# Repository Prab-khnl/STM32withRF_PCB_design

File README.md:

Chip used :- STM32WB55CEU6.

Important Online Note :-
<https://www.st.com/resource/en/application_note/an5165-how-to-develop-rf-hardware-using-stm32wb-microcontrollers-stmicroelectronics.pdf>

![A diagram of a circuit board AI-generated content may be
incorrect.](images/media/image1.png)This is the reference :-

Use STM32CubeIDE to get more information about the Chip :-

![A screenshot of a computer AI-generated content may be
incorrect.](images/media/image2.png)

![A screenshot of a computer AI-generated content may be
incorrect.](images/media/image3.png)Here I have enabled I2C on PB8 and PB9
corresponding to Pin 5 and 6 respectively.

In Kicad, import the board STM32WB55CEUX.

Ground the Pins VSS5MP5, VSSRF and VSS.

![A screen shot of a computer AI-generated content may be
incorrect.](images/media/image4.png)

As illustrated on the reference manual, the Pin VDDUSB, VDDA, VDD, VDD,
VDD and VBAT are connected to 3.3V power supply through bigger capacitor
(4.67uF) and smaller capacitors (100nF : local supply).

![A screen shot of a graph AI-generated content may be
incorrect.](images/media/image5.png)

For VDDRF, connect it to 100nF capacitor along with power supply

![A screenshot of a computer AI-generated content may be
incorrect.](images/media/image6.png)

We need Stepdown converter to step down voltage for lower voltage. For 8
MHz we use 2.2uH inductor and for 4MHz we use 10uF inductor. SMPSLX --
Switch Mode Power Supply

SMPSFB -- Switch Power Supply Feed Back

![A screenshot of a computer AI-generated content may be
incorrect.](images/media/image7.png)

The low frequency oscillator(Crystal) is connected to Pin 2 and 3.

![A screenshot of a computer AI-generated content may be
incorrect.](images/media/image8.png)

![A screenshot of a computer AI-generated content may be
incorrect.](images/media/image9.png)The high frequency
oscillator(Crystal_GND24) are connected to Pin 24 and 25.

We can add resistor in HSC_IN to increase the longevity of oscillator.

![A diagram of a circuit AI-generated content may be
incorrect.](images/media/image10.png)RF Section:-

We need low pass filter for 2.4GHz and 5GHz.

For that we need to create a footprint and symbol of DLF162500LT-5028A1.

![A screenshot of a computer AI-generated content may be
incorrect.](images/media/image11.png)From File, Add library\> DLF162500LT-5028A1

![A screenshot of a computer AI-generated content may be
incorrect.](images/media/image12.png)Go to the Pin table and add pins.

Use the rectangle tool on the right side to draw the rectangle touching
the pins.![A screen shot of a computer AI-generated content may be
incorrect.](images/media/image13.png)

Use the Text "T" tool to add the text label "2.4GHz- 2.5GHz".

Save the symbol. Now it's time to create the physical footprint of the
symbol.

Use this footprint editor to create the new footprint.![A screenshot of
a computer AI-generated content may be
incorrect.](images/media/image14.png)

Go to file \> Add library and name your library.

Here the newly added library is STM32_RF_LowPassFilterFootPrint

![A screenshot of a computer AI-generated content may be
incorrect.](images/media/image15.png)

In the new library, add new Footprint and name it as Component name eg.
"DLF162500LT-5028A1"

This is the dimension of
[footprint](https://product.tdk.com/system/files/dam/doc/product/rf/rf/filter/catalog/rf_lpf_dlf162500lt-5028a1_en.pdf).

![A blueprint of a diagram AI-generated content may be
incorrect.](images/media/image16.png)

![A screenshot of a phone AI-generated content may be
incorrect.](images/media/image17.png)Add pad from here.

According to the dimension, the centre of origin:-

X : ½ ( 0.275 + 0.45) + 0.25 = 0.6125.

Y : ½ (0.245 +0.21) = 0.2275

This is the position and dimensions of pad1 :-

![A screenshot of a computer AI-generated content may be
incorrect.](images/media/image18.png)

This is the position and dimensions of pad 3:-

![A screenshot of a computer AI-generated content may be
incorrect.](images/media/image19.png)

This is the position and dimensions of pad 2:-

![A screenshot of a computer AI-generated content may be
incorrect.](images/media/image20.png)

This is the position and dimensions of pad 4:-

![A screenshot of a computer AI-generated content may be
incorrect.](images/media/image21.png)

Download 3D Model of symbol from ![A screenshot of a computer
AI-generated content may be
incorrect.](images/media/image22.png)ultralibrarian in .step format.

![A screenshot of a computer AI-generated content may be
incorrect.](images/media/image23.png)In Kicad go to footprint properties and
add the 3d model. Our pad aligns with physical pins.

![A screen shot of a computer AI-generated content may be
incorrect.](images/media/image24.png)With silkscreen layer selected, click
circle tool to add indicator for pin 1.

Using the symbol editor, assign newly created footprint to the symbol we
just created.

![A screenshot of a computer AI-generated content may be
incorrect.](images/media/image25.png)

Place newly created symbol to the schematic and connect to pin 1.![A
diagram of a circuit AI-generated content may be
incorrect.](images/media/image26.png)

Add a Co-Axial connector.

![A screenshot of a computer AI-generated content may be
incorrect.](images/media/image27.png)

![A computer diagram of a circuit board AI-generated content may be
incorrect.](images/media/image28.png)This is our current progress.

Now, we need to add the programming interface.

The PA 13, PA 14 and PA3 can be used to program and debug the board.
Along with those pins NRST has to be low (0) for programming mode and
high (1) on normal mode.

![A screenshot of a computer AI-generated content may be
incorrect.](images/media/image29.png)

Connect the tag connector "Conn_ARM_SWD_TagConnect_TC2030". Connect the
tag connector to respective pin as shown. For NRST( Reset) pin connect
it through 100nF capacitor at Pin 7.

![A diagram of a circuit board AI-generated content may be
incorrect.](images/media/image30.png)

PH3 is bootload pin and should 0 be on bootload. When the pin Switch is
not pressed, the PH3 is grounded but on pressed, the connection acts as
lowpass RC filter.

![A diagram of a circuit AI-generated content may be
incorrect.](images/media/image31.png)

Add USB "USB_C_Receptacle_USB2.0_16P" and we are going to use pin 37 and
38.

![A computer screen shot of a circuit board AI-generated content may be
incorrect.](images/media/image32.png)

Add a USB protector between the USB Connector and Pins.

![A diagram of a circuit board AI-generated content may be
incorrect.](images/media/image33.png)

The D- pins and D+ pins are connected each other and then to Pins 1 and
3 respectively on the USB protector. The VBUS is connected to Pin 5. Pin
6 and 4 are connected to Pin 37 and 37 respectively on the STM32
Microcontroller.

The pull down resistors are tied on the Pin A5 and B5.

Convert 5V of VBUS to 3.3V using LDO voltage regulator.

Search LDO voltage regulator by putting requirement on mouser. Add a
voltage regulator "MIC5365-3.3YD5" to get 3.3V output.

![A computer circuit board with many wires AI-generated content may be
incorrect.](images/media/image34.png)

![A diagram of a circuit AI-generated content may be
incorrect.](images/media/image35.png)Add a Peripheral connection on PA2 and PA2
using Generic 01\*04 Connector.

![A screenshot of a computer AI-generated content may be
incorrect.](images/media/image36.png)Use PA7 for PWM Output signal generation.

Add LED to Pin 16 (PA7) and add current limiting 220 Ohm resistor.

![A screenshot of a computer AI-generated content may be
incorrect.](images/media/image37.png)

![A computer diagram of a circuit board AI-generated content may be
incorrect.](images/media/image38.png)Overall schematic :-

![A computer screen shot of a computer program AI-generated content may
be incorrect.](images/media/image39.png)Run electric rule checker and make sure all
wirings are correct.

Add footprint to the capacitor.

Add footprint to all the components.

![A screenshot of a computer AI-generated content may be
incorrect.](images/media/image41.png)

Create Bill of Materials for all the components.

![A screenshot of a computer AI-generated content may be
incorrect.](images/media/image42.png)

![A screenshot of a computer AI-generated content may be
incorrect.](images/media/image43.png)Add netclass to group the components.

Setup layers

![A screenshot of a computer AI-generated content may be
incorrect.](images/media/image44.png)

Select 4 layers and impedance controlled

![A screenshot of a computer AI-generated content may be
incorrect.](images/media/image45.png)

![A screenshot of a computer AI-generated content may be
incorrect.](images/media/image46.png)Select these layer width

Lead free copper

![A screenshot of a computer AI-generated content may be
incorrect.](images/media/image47.png)

Solder Mask

![A screenshot of a computer AI-generated content may be
incorrect.](images/media/image48.png)

![A screenshot of a computer AI-generated content may be
incorrect.](images/media/image49.png)Fill in these board capabilities and
requirements

![A screenshot of a computer AI-generated content may be
incorrect.](images/media/image50.png)Board rule

![A screenshot of a computer AI-generated content may be
incorrect.](images/media/image51.png)These tracks are calculated on 50 ohm
impedance.

Press Ok

Multi layer PCB![A diagram of a layer of copper layer AI-generated
content may be
incorrect.](images/media/image52.png)

Press F8 to apply the footprints

![A computer screen shot of a computer AI-generated content may be
incorrect.](images/media/image53.png)This is the current 3D view:-

Update the 3D Model STEP file for J2 connector downloaded from
[MOLEX](https://www.molex.com/en-us/products/part-detail/530480410).

![A computer screen shot of a computer AI-generated content may be
incorrect.](images/media/image54.png)

Add 3D model for STM32 from
[here](https://gitlab.com/kicad/libraries/kicad-packages3D/-/blob/5.1.10/Package_DFN_QFN.3dshapes/QFN-48-1EP_7x7mm_P0.5mm_EP5.6x5.6mm.step)

![A screenshot of a computer AI-generated content may be
incorrect.](images/media/image55.png)

3d model can be downloaded from here:-

> 3D content central
>
> Grabcad

![A screenshot of a computer AI-generated content may be
incorrect.](images/media/image56.png)Select blue color for SWD routing

Select net colors to blue for all

![A screenshot of a computer AI-generated content may be
incorrect.](images/media/image57.png)Do the same all others

Create a layout

Select 1 mmm grid

![A machine with colorful lights AI-generated content may be
incorrect.](images/media/image58.png)Move the chip by moving around with M.

Move critical section first like RF, USB connector close to
microcontroller. Also keep crystal and power close to microcontroller.

Debug,BOOT0 , Reset, TX and RX are less critical. BI coupling capacitor
needs to be close .

![A computer screen shot of a computer chip AI-generated content may be
incorrect.](images/media/image59.png)Keep Connector to left of IC.

Place USB connector to left of tag connector and rotate as indicated.

![A computer screen shot of a computer chip AI-generated content may be
incorrect.](images/media/image60.png)

![A computer screen shot of a computer AI-generated content may be
incorrect.](images/media/image61.png)Place RF connector to right of IC and place
filter in between the IC and connector.

Place the crystal as indicated.

![A computer chip with many colors AI-generated content may be
incorrect.](images/media/image62.png)

![A computer screen shot of a computer chip AI-generated content may be
incorrect.](images/media/image63.png)Place the L1, L2 and C14 to top of IC for
now

Place UART connector and resistor to bottom of IC.

![A computer chip with many different colors AI-generated content may be
incorrect.](images/media/image64.png)

![A computer screen shot of a computer AI-generated content may be
incorrect.](images/media/image65.png)Place USB protector as shown

Place the RF components as shown

![A screenshot of a video game AI-generated content may be
incorrect.](images/media/image66.png)

![A computer chip with many different components AI-generated content
may be incorrect.](images/media/image67.png)This is the current 3D view

Place capacitor to crystal oscillator

![A computer screen shot of a computer AI-generated content may be
incorrect.](images/media/image68.png)

![A computer screen shot of a computer AI-generated content may be
incorrect.](images/media/image69.png)Finetune this SMP power supply layout.

Place RF decoupling capacitor close to Pad 23

![A screenshot of a computer AI-generated content may be
incorrect.](images/media/image70.png)

Place another capacitor for pin 20

![A screenshot of a computer AI-generated content may be
incorrect.](images/media/image71.png)

Place capacitor like this near pin 40 to make room to route trace for
Serial DIO

![A computer chip with numbers and symbols AI-generated content may be
incorrect.](images/media/image72.png)

Place decoupling capacitor for pin 34 and 35

![A screenshot of a computer AI-generated content may be
incorrect.](images/media/image73.png)

![A computer chip with many different colored lights AI-generated
content may be
incorrect.](images/media/image74.png)Re arrange this section

Make a room for reset pin

![A computer chip with many different colored lights AI-generated
content may be
incorrect.](images/media/image75.png)

![A computer screen shot of a computer chip AI-generated content may be
incorrect.](images/media/image76.png)Move SMP close to microcontroller but put crystal
away

![A screenshot of a video game AI-generated content may be
incorrect.](images/media/image77.png)Place LDO 3.3V regulator as shown

Place resistors around USB C connector

![A computer screen shot of a computer AI-generated content may be
incorrect.](images/media/image78.png)

Place reset capacitor C13

![A computer chip with many different colors AI-generated content may be
incorrect.](images/media/image79.png)

Place the switch and resistors around the switch

![A computer screen shot of a computer AI-generated content may be
incorrect.](images/media/image80.png)

![A computer chip with many different components AI-generated content
may be incorrect.](images/media/image81.png)This is the current 3D layout of the board

![A computer screen shot of a computer program AI-generated content may
be incorrect.](images/media/image82.png)Define board out line. Select Edge.cuts
layer. Select line tool and draw the line.

You can also use the arc tool to draw the arc around the edge of the
board

![A screen shot of a computer AI-generated content may be
incorrect.](images/media/image83.png)

Start routing with most critical component. We can use top layer for
power and bottom layer for ground.

Signal -- GND -GND -Signal ( 4 layers) GNB Layer in Inner 1 and Inner 2

![A screenshot of a computer AI-generated content may be
incorrect.](images/media/image84.png)Select In1.Cu. Add a GND Layer and adjust
the electrical properties.

Draw outline of the board. Select B to fill the board.

![A computer screen shot of a circuit board AI-generated content may be
incorrect.](images/media/image85.png)

Add a mounting hole with this footprint.\
![A screenshot of a computer AI-generated content may be
incorrect.](images/media/image86.png)

Add fiducial marker to automate assembly.

![A screenshot of a computer AI-generated content may be
incorrect.](images/media/image87.png)

![A computer screen shot of a computer AI-generated content may be
incorrect.](images/media/image88.png)Place the mounting hole and marker as
shown.

Use Via to jump between layer 0.7mm/0.33mm via

![A screenshot of a computer AI-generated content may be
incorrect.](images/media/image89.png)

![A screenshot of a computer AI-generated content may be
incorrect.](images/media/image90.png)Connect the via and track with GND Pad

Copy and paste these tracks and via on 0402 components.

![A computer screen shot of a computer chip AI-generated content may be
incorrect.](images/media/image91.png)

Place the via on the chips for heat sinking purpose.

![A green screen with white text AI-generated content may be
incorrect.](images/media/image92.png)

![A computer screen shot of a computer chip AI-generated content may be
incorrect.](images/media/image93.png)Add 3.3V via

For RF trace we would use 0.190mm trace for control impedance of 50 Ohm

![A screenshot of a computer AI-generated content may be
incorrect.](images/media/image94.png)Set the width of RF in NetClass properties.

![A computer screen shot of a computer AI-generated content may be
incorrect.](images/media/image95.png)Route the RF section

Route the high frequency HSC clock.

![A computer screen shot of a circuit board AI-generated content may be
incorrect.](images/media/image96.png)

![A computer screen shot of a circuit board AI-generated content may be
incorrect.](images/media/image97.png)Trace Low frequency clocks

Add 0.250 mm track width for Switch Model. Press W to increase the mad
width.

![A screenshot of a computer AI-generated content may be
incorrect.](images/media/image98.png) We can also use this for the feedback

Ground the Pin

![A screen shot of a computer AI-generated content may be
incorrect.](images/media/image99.png)

Use differential pair by pressing 6 and selecting the netclass "USB" to
route the two usb wires together

![A screenshot of a computer AI-generated content may be
incorrect.](images/media/image100.png)Route the rest

![A computer screen shot of a circuit board AI-generated content may be
incorrect.](images/media/image101.png)

![A screenshot of a computer AI-generated content may be
incorrect.](images/media/image102.png)Route the UART Section

![A computer screen shot of a circuit board AI-generated content may be
incorrect.](images/media/image103.png)Use Via to jump between top and bottom
layer to route the Boot0

![A computer screen shot of a computer AI-generated content may be
incorrect.](images/media/image104.png)We can place the GND via near transitional jump for
higher bandwidth circuit

![A computer screen shot of a circuit board AI-generated content may be
incorrect.](images/media/image105.png)Complete the rest of the USB connector section.

Complete the led section

![A screenshot of a video game AI-generated content may be
incorrect.](images/media/image106.png)

Select Mounting hole. Select 2 and Press E to change the copper zones to
Solid

![A screenshot of a computer AI-generated content may be
incorrect.](images/media/image107.png)

![A computer screen shot of a circuit board AI-generated content may be
incorrect.](images/media/image108.png)Connect the 5Vs power supply traces and
draw polygon layer for 3V power supply.

![A computer screen shot of a star AI-generated content may be
incorrect.](images/media/image109.png)Select only the bottom select by selecting
"Hide all planes but active" and draw traces connecting 3.3V Vias

The other way to do is to convert the bottom layer polygon to 3.3V
layer. For that select the GNB polygon, Crl +C and paste it. Press E to
select the new layer and select 3.3V for bottom layer

![A screenshot of a computer AI-generated content may be
incorrect.](images/media/image110.png)

![A screenshot of a video game AI-generated content may be
incorrect.](images/media/image111.png)Now, 3.3V is the bottom layer.

![A computer screen shot of a computer chip AI-generated content may be
incorrect.](images/media/image112.png)Connect rest of the 3.3V and GNB
connections

For copper balancing, change the top copper layer to GND. To do this
Select In1.cu and double click on GND layer. Choose F.CU to GND Layer.

![A screenshot of a computer AI-generated content may be
incorrect.](images/media/image113.png)

Press B to repull and now we have GND layer on top layer.

![A computer screen shot of a circuit board AI-generated content may be
incorrect.](images/media/image114.png)

These coppers which are really close could affect the impedance for the
RF section. The traces should be at least 3 times the dielectric width
away.

![A video game screen with a green background AI-generated content may
be incorrect.](images/media/image115.png)

Currently the dielectric is 0.1mm. We want the separation to be at least
0.3mm.

![A screenshot of a computer AI-generated content may be
incorrect.](images/media/image116.png)

Draw keypad area to keep out the copper fills.

![A screenshot of a computer AI-generated content may be
incorrect.](images/media/image117.png)

Press B to keep out the copper fills.

![A screenshot of a video game AI-generated content may be
incorrect.](images/media/image118.png)

![A screenshot of a computer AI-generated content may be
incorrect.](images/media/image119.png)Instead, we can also change the clearance
to 0.35mm.

![A screenshot of a computer AI-generated content may be
incorrect.](images/media/image120.png)We can also try thermal relief to have
smaller gap and larger spoke width.

We need to Stitching via to reduce impedance between ground plane and
vias. Place it around the board. The spacing can be calculated as

(3 \* 10\^8)/ (20\* sqrt(4.29) \*2.4\*10\^9) \*10\^3

Speed of light / 20 \* Sqrt of dielectric constant \* Frequency

=3mm

![A computer screen shot of a circuit board AI-generated content may be
incorrect.](images/media/image121.png)

![A green circuit board with many small chips AI-generated content may
be incorrect.](images/media/image122.png)This is what the board looks like

Move the marking on the silkscreen so that the markings do not overlap.

![A computer screen shot of a computer chip AI-generated content may be
incorrect.](images/media/image123.png)

We can add teardrops for smooth transition between wide and narrow
traces. Else, go to tools\> Remove unused pads

![A screenshot of a computer AI-generated content may be
incorrect.](images/media/image124.png)

Run DRC Checker.

Fix clearance violation by decreasing the pad size.

![A screen shot of a computer AI-generated content may be
incorrect.](images/media/image125.png)

Reduce the pad size in X axis.

![A screenshot of a computer AI-generated content may be
incorrect.](images/media/image126.png)

To solve this error, uncheck the fiducial marker pad from F.Cu.

![A screenshot of a computer AI-generated content may be
incorrect.](images/media/image127.png)

To fix it, connect the pad to GND via.

Clearance violation

![A screenshot of a computer AI-generated content may be
incorrect.](images/media/image129.png)

Move the GND via.

![A computer screen shot of a green and red line AI-generated content
may be
incorrect.](images/media/image130.png)

Now, we have 0 DRC violation

![A computer screen shot of a computer AI-generated content may be
incorrect.](images/media/image131.png)

Final Board:-

![A computer screen shot of a green circuit board AI-generated content
may be
incorrect.](images/media/image132.png)

Go to Tools \> Generate Bill of Materials to generate the components
needed and their designator values on the PCB.

![A screenshot of a computer AI-generated content may be
incorrect.](images/media/image133.png)

We need to know the coordinate of the components to know where the
components are on the PCB.

At the Place \> Grid Place Origin and Drill Place Origin, put the origin
to bottom left.

![A green screen with black dots and white text AI-generated content may
be incorrect.](images/media/image134.png)

Go to files \> Fabrication Output \> Generate Placement files

![A screenshot of a computer AI-generated content may be
incorrect.](images/media/image135.png)

.pos file will appear on the project directory.

We now need the Gerber files. Go to files \> Fabrication Output \>
Generate Gerber files. Include the following layers and options.

![A screenshot of a computer AI-generated content may be
incorrect.](images/media/image136.png)

Go to generate layers and generate drill files.

You can check the gerber files using Kicad Gerber viewer. These are the
files we need to upload to manufacturer ( Gerber, Position files and
Bill of Materials). We can also send additional notes such as Control
Impedance, clearance and so on.

![A computer screen shot of a computer AI-generated content may be
incorrect.](images/media/image137.png)

To order the PCB, create and upload zip files of Gerber.

![A screenshot of a computer AI-generated content may be
incorrect.](images/media/image138.png)

It automatically identified the board requirements

![A screenshot of a computer AI-generated content may be
incorrect.](images/media/image139.png)

![A screenshot of a computer AI-generated content may be
incorrect.](images/media/image140.png)Select these options

We can have PCBway assemble the whole PCB

![A screenshot of a computer AI-generated content may be
incorrect.](images/media/image141.png)

Then you will have to upload Bill of Material files, Centroid files
(CPL.txt) and assembly drawing optional).

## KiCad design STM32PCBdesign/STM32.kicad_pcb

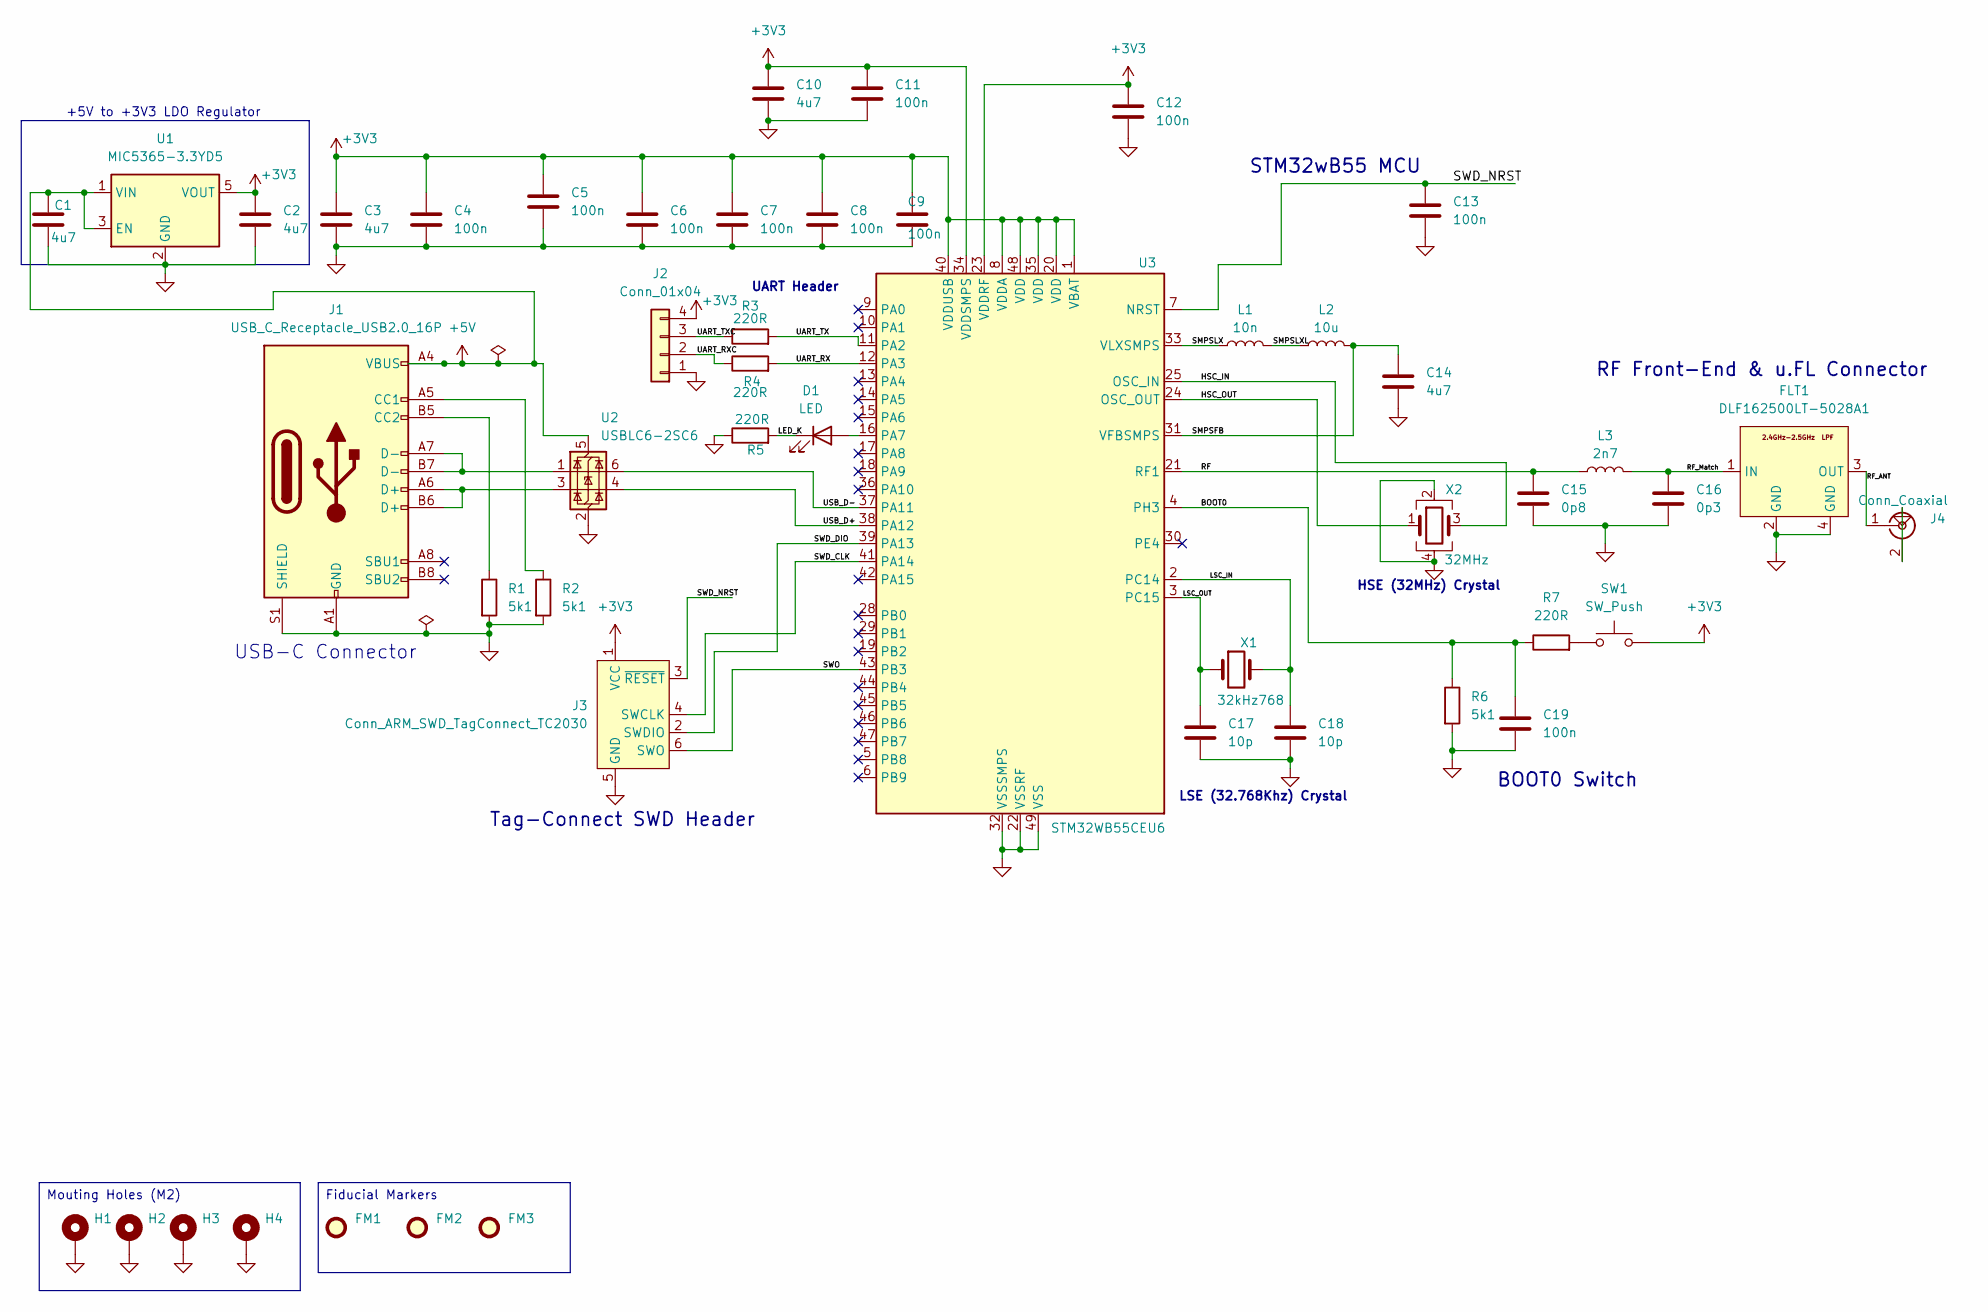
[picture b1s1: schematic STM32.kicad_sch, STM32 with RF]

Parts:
C1, C2, C3, C10, C14: 4u7; C_0603_1608Metric; Manufacturer Part Number 0603YD475MAT2A
C4, C5, C6, C7, C8, C9, C11, C12, C13, C19: 100n; C_0402_1005Metric; Manufacturer Part Number 04023C104KAT2A
C15: 0p8; C_0402_1005Metric; Manufacturer Part Number GRM1555C1HR80BA01D
C16: 0p3; C_0402_1005Metric; Manufacturer Part Number GRM1555C1HR30WA01D
C17, C18: 10p; C_0402_1005Metric; Manufacturer Part Number 04025A100JAT4A
D1: LED; LED_0402_1005Metric; Manufacturer Part Number 150040RS73240
FLT1: DLF162500LT-5028A1; Manufacturer Part Number DLF162500LT-5028A1
FM1, FM2, FM3: Fiducial; Fiducial_1mm_Mask2mm
H1, H2, H3, H4: MountingHole_Pad; MountingHole_2.2mm_M2_Pad_Via
J1: USB_C_Receptacle_USB2.0_16P; USB_C_Receptacle_GCT_USB4105-xx-A_16P_TopMnt_Horizontal; Manufacturer Part Number USB4105-GF-A
J2: Conn_01x04; Molex_CLIK-Mate_502386-0470_1x04-1MP_P1.25mm_Horizontal; Manufacturer Part Number 53048-0410
J3: Conn_ARM_SWD_TagConnect_TC2030; Tag-Connect_TC2030-IDC-FP_2x03_P1.27mm_Vertical
J4: Conn_Coaxial; U.FL_Hirose_U.FL-R-SMT-1_Vertical; Manufacturer Part Number U.FL-R-SMT(01)
L1: 10n; L_0402_1005Metric; Manufacturer Part Number LQG15HS18NJ02D
L2: 10u; L_0805_2012Metric; Manufacturer Part Number LQM21FN100M70L
L3: 2n7; L_0402_1005Metric; Manufacturer Part Number LQG15HS2N7S02D
R1, R2, R6: 5k1; R_0402_1005Metric; Manufacturer Part Number RC0603FR-075K1L
R3, R4, R5, R7: 220R; R_0402_1005Metric; Manufacturer Part Number RC0402FR-07221RL
SW1: SW_Push; SW_SPST_CK_RS282G05A3; Manufacturer Part Number RS282G05A3SMRT
U1: MIC5365-3.3YD5; TSOT-23-5; Manufacturer Part Number MIC5365-3.3YC5-TR
U2: USBLC6-2SC6; SOT-23-6; Manufacturer Part Number USBLC6-2SC6
U3: STM32WB55CEU6; QFN-48-1EP_7x7mm_P0.5mm_EP5.6x5.6mm; Manufacturer Part Number STM32WB55CEU6
X1: 32kHz768; Crystal_SMD_2012-2Pin_2.0x1.2mm; Manufacturer Part Number NX2012SA-32.768K-STD-MUB-1
X2: 32MHz; Crystal_SMD_2016-4Pin_2.0x1.6mm; Manufacturer Part Number NX2016SA-32M-EXS00A-CS06465

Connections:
+3V3: C2.1, C3.1, C4.1, C5.1, C6.1, C7.1, C8.1, C9.1, C10.1, C11.1, C12.1, J2.4, J3.1 (VCC), SW1.2, U1.5 (VOUT), U3.1 (VBAT), U3.8 (VDDA), U3.20 (VDD), U3.23 (VDDRF), U3.34 (VDDSMPS), U3.35 (VDD), U3.40 (VDDUSB), U3.48 (VDD)
+5V: C1.1, J1.A4 (VBUS), J1.A9 (VBUS), J1.B4 (VBUS), J1.B9 (VBUS), U1.1 (VIN), U1.3 (EN), U2.5 (VBUS)
/BOOT0: C19.1, R6.1, R7.1, U3.4 (PH3)
/HSC_IN: U3.25 (OSC_IN), X2.3
/HSC_OUT: U3.24 (OSC_OUT), X2.1
/LED_K: D1.1 (K), R5.2
/LSC_IN: C18.1, U3.2 (PC14), X1.2
/LSC_OUT: C17.1, U3.3 (PC15), X1.1
/RF: C15.1, L3.1, U3.21 (RF1)
/RF_ANT: FLT1.3 (OUT), J4.1 (In)
/RF_Match: C16.1, FLT1.1 (IN), L3.2
/SMPSFB: C14.1, L2.2, U3.31 (VFBSMPS)
/SMPSLX: L1.1, U3.33 (VLXSMPS)
/SMPSLXL: L1.2, L2.1
/SWD_CLK: J3.4 (SWCLK), U3.41 (PA14)
/SWD_DIO: J3.2 (SWDIO), U3.39 (PA13)
/SWD_NRST: C13.1, J3.3 (~RESET), U3.7 (NRST)
/SWO: J3.6 (SWO), U3.43 (PB3)
/UART_RX: R4.2, U3.12 (PA3)
/UART_RXC: J2.2, R4.1
/UART_TX: R3.2, U3.11 (PA2)
/UART_TXC: J2.3, R3.1
/USB_D+: U2.4 (I/O2), U3.38 (PA12)
/USB_D-: U2.6 (I/O1), U3.37 (PA11)
GND: C1.2, C2.2, C3.2, C4.2, C5.2, C6.2, C7.2, C8.2, C9.2, C10.2, C11.2, C12.2, C13.2, C14.2, C15.2, C16.2, C17.2, C18.2, C19.2, FLT1.2 (GND), FLT1.4 (GND), H1.1, H2.1, H3.1, H4.1, J1.A1 (GND), J1.A12 (GND), J1.B1 (GND), J1.B12 (GND), J1.S1 (SHIELD), J2.1, J3.5 (GND), J4.2 (Ext), R1.2, R2.2, R5.1, R6.2, U1.2 (GND), U2.2 (GND), U3.22 (VSSRF), U3.32 (VSSSMPS), U3.49 (VSS), X2.2, X2.4
unnamed: D1.2 (A), U3.16 (PA7)
unnamed: J1.A5 (CC1), R2.1
unnamed: J1.B5 (CC2), R1.1
unnamed: J1.A6 (D+), J1.B6 (D+), U2.3 (I/O2)
unnamed: J1.A7 (D-), J1.B7 (D-), U2.1 (I/O1)
unnamed: R7.2, SW1.1

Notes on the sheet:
BOOT0 Switch
RF Front-End & u.FL Connector
UART Header
+5V to +3V3 LDO Regulator
STM32wB55 MCU
Tag-Connect SWD Header
HSE (32MHz) Crystal
USB-C Connector
LSE (32.768Khz) Crystal
Fiducial Markers
Mouting Holes (M2)

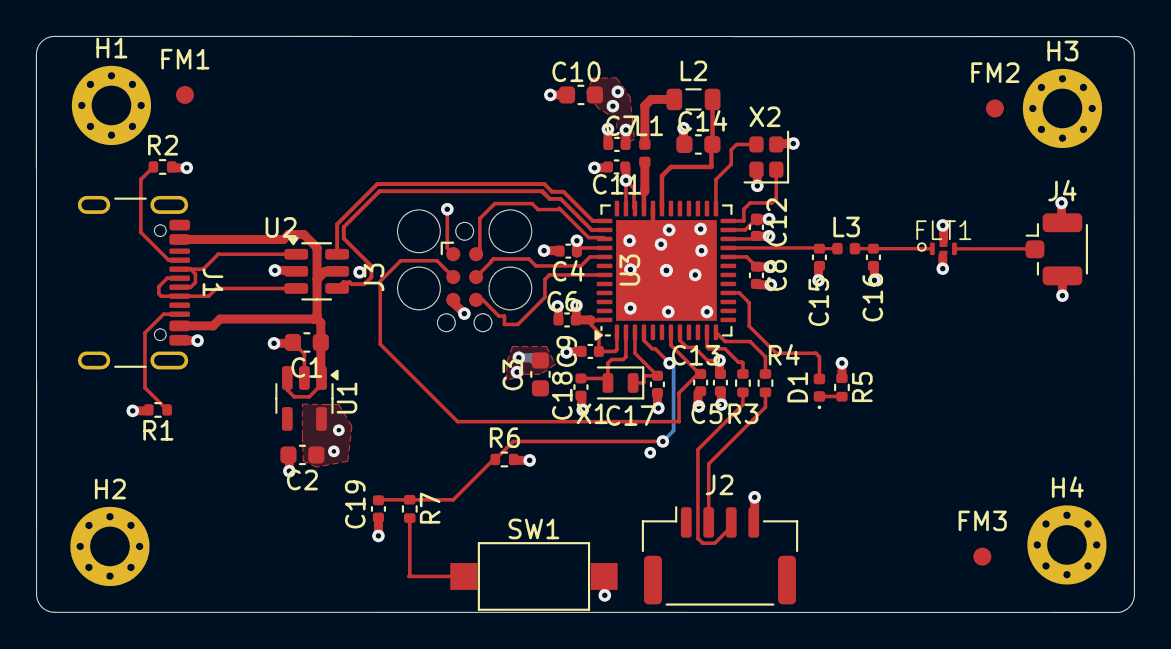
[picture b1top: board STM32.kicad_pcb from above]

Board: 4 copper layers, 61.0 x 32.0 mm, 48 parts (0 on the bottom side), 31 nets.

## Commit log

2025-05-20 Linking images to .md
2025-06-15 PCB design and Schematics
2025-06-15 Final PCB design walkthrough
